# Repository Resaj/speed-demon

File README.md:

# Speed Demon
Speed Demon es mi primer velocista de competición. Ha participado en Alcabot y Cosmobot.

Es un robot bastante casero porque lo hice en 10 días con una plancha de acero que posteriormente cubrí de laca para que no se oxidara.
Para su primera competición tuve que cambiarle la placa del microcontrolador la tarde de antes porque la inicial daba muchos problemas. Le programé el algoritmo PID en una noche y a la mañana siguiente compitió incluso con aceleración en recta programada un rato antes.

Dio muy buenos resultados y quedó en una posición bastante digna, pero pronto fue sustituido por Pumatrón V2 en su versión velocista.
Los programas "actuales" de Speed Demon que he subido al repositorio quedaron en versión beta precisamente por eso.

## Autor
[Rubén Espino San José](https://github.com/Resaj)

## License

Todos estos productos están liberados mediante [Creative Commons Attribution-ShareAlike 4.0 International License](http://creativecommons.org/licenses/by-sa/4.0/).  
_All these products are released under [Creative Commons Attribution-ShareAlike 4.0 International License](http://creativecommons.org/licenses/by-sa/4.0/)._

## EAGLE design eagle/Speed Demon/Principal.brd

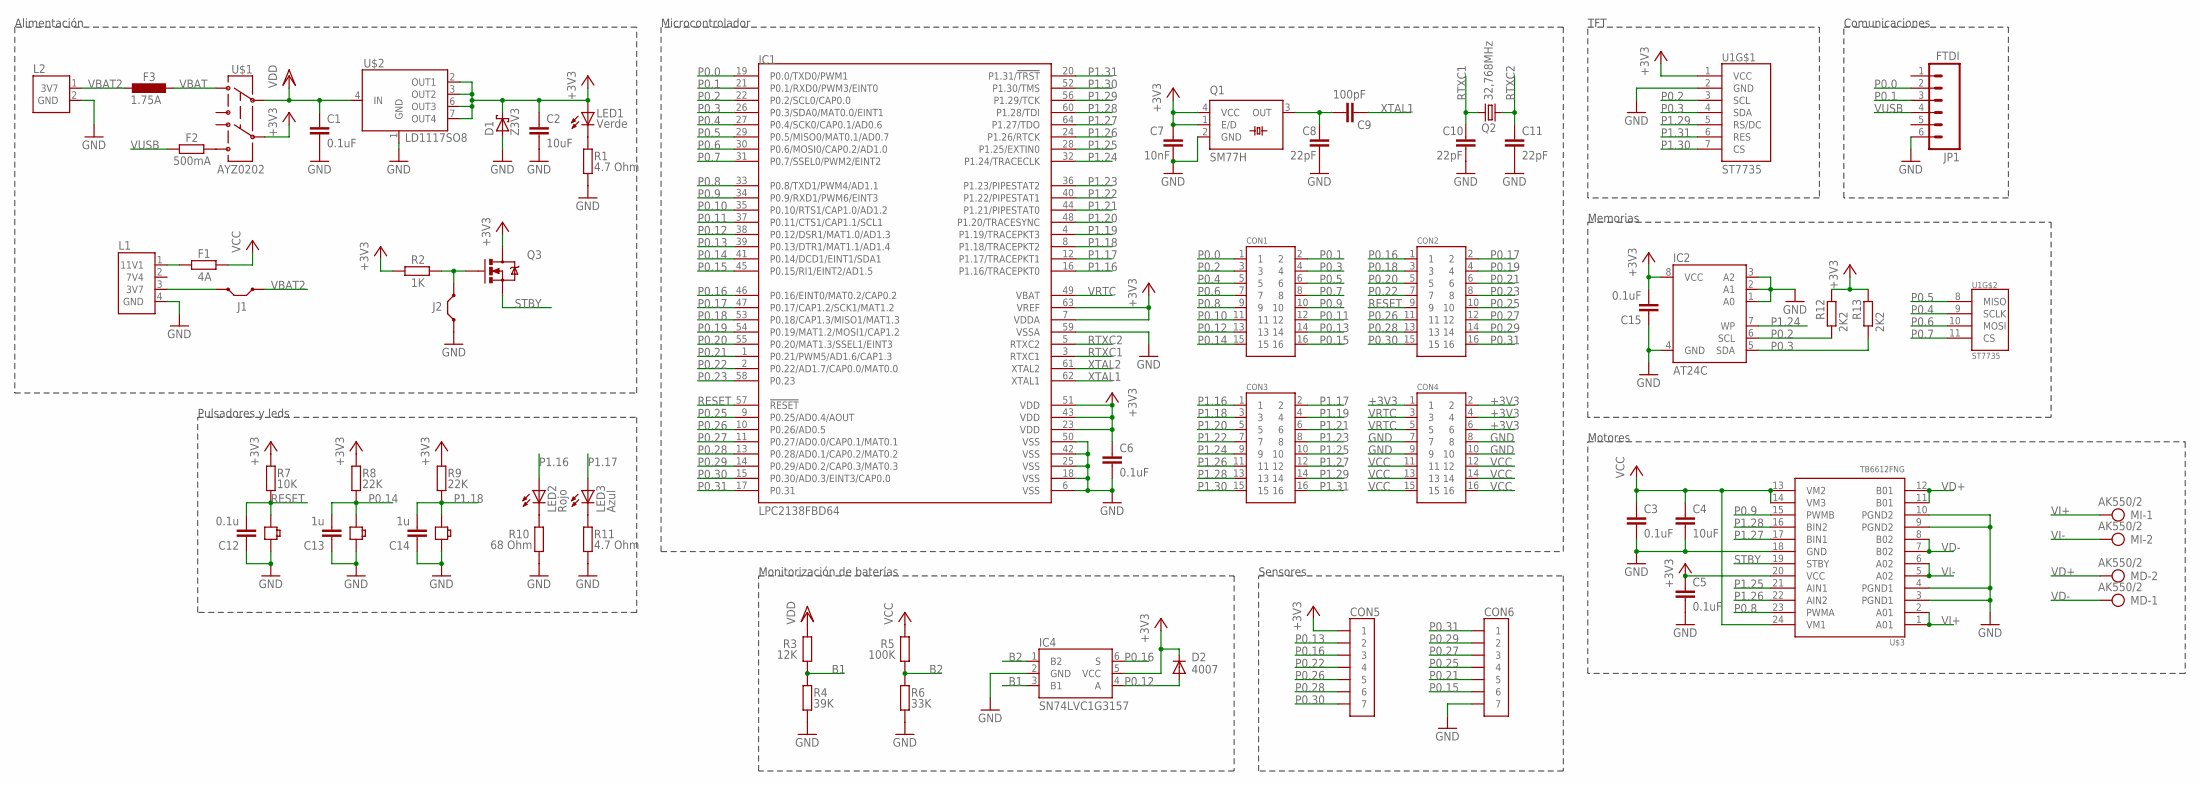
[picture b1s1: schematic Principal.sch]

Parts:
B1: BUTTON-SMD-2P; BUTTON_2P_SMD
C1, C3, C5, C6, C15: 0.1uF; C0805
C2, C4: 10uF; C1206
C7: 10nF; C0805
C8, C10, C11: 22pF; C0805
C9: 100pF; C0805
C12: 0.1u; C0805
C13, C14: 1u; C0805
CON1, CON2, CON3, CON4: 8X2_PIN_2MM_HEMBRA; 8X2_PIN_2MM
CON5, CON6: 7_PINES; 7_PIN_MACHO_SMD_RA
D1: Z3V3; DO35-7
D2: 4007; SOD106-R
F1: 4A; 2920
F2: 500mA; M1206
F3: 1.75A; L1812
IC1: LPC2138FBD64; TSQFP50P1200X1200X160-64N
IC2: AT24C; 8S1
IC4: SN74LVC1G3157; DBV
J1, J2: JUMPERSMD; 2_PIN_VERT_SMD
JP1: FTDI; 1X06_SMD_STRAIGHT
L1: CONECTOR_LIPO_11.1V
L2: CONECTOR_LIPO_3.7V
LED1: Verde; CHIPLED_0805
LED2: Rojo; CHIPLED_0805
LED3: Azul; CHIPLED_0805
LOAD: BUTTON-SMD-2P; BUTTON_2P_SMD
MD: AK550/2
MI: AK550/2
Q1: SM77H
Q2: 32,768MHz; TC38H
Q3: MOSFET-NCHANNELSMD; SOT23-3
R1, R11: 4.7 Ohm; R0805
R2: 1K; R0805
R3: 12K; R0805
R4: 39K; R0805
R5: 100K; R0805
R6: 33K; R0805
R7: 10K; R0805
R8, R9: 22K; R0805
R10: 68 Ohm; R0805
R12, R13: 2K2; R0805
RESET: BUTTON-SMD-2P; BUTTON_2P_SMD
U1: ST7735
U$1: AYZ0202
U$2: LD1117SO8; SO8
U$3: TB6612FNG; SSOP24

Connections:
7V4: L1.2 (7V4)
+3V3: C2.1, C5.1, C6.1, C7.1, C15.2, CON4.1, CON4.2, CON4.4, CON4.6, CON5.P$1 (1), D1.C, D2.C, IC1.7 (VDDA), IC1.23 (VDD), IC1.43 (VDD), IC1.51 (VDD), IC1.63 (VREF), IC2.8 (VCC), IC4.5 (VCC), LED1.A, Q1.1 (E/D), Q1.4 (VCC), Q3.3 (D), R2.2, R7.2, R8.2, R9.2, R12.2, R13.2, U1.1 (VCC), U$1.5, U$2.2 (OUT1), U$2.3 (OUT2), U$2.6 (OUT3), U$2.7 (OUT4), U$3.20 (VCC)
B1: IC4.3 (B1), R3.1, R4.2
B2: IC4.1 (B2), R5.1, R6.2
GND: B1.P$2, C1.2, C2.2, C3.2, C4.2, C5.2, C6.2, C7.2, C8.2, C10.2, C11.2, C12.1, C13.1, C14.1, C15.1, CON4.7, CON4.8, CON4.9, CON4.10, CON6.P$7 (7), D1.A, IC1.6 (VSS), IC1.18 (VSS), IC1.25 (VSS), IC1.42 (VSS), IC1.50 (VSS), IC1.59 (VSSA), IC2.1 (A0), IC2.2 (A1), IC2.3 (A2), IC2.4 (GND), IC4.2 (GND), J2.1, JP1.6, L1.4 (GND), L2.2 (GND), LOAD.P$2, Q1.2 (GND), R1.2, R4.1, R6.1, R10.2, R11.2, RESET.P$2, U1.2 (GND), U$2.1 (GND), U$3.3 (PGND1), U$3.4 (PGND1), U$3.9 (PGND2), U$3.10 (PGND2), U$3.18 (GND)
unnamed: LED2.C, R10.1
unnamed: LED3.C, R11.1
unnamed: J2.2, Q3.1 (G), R2.1
unnamed: F2.1, U$1.4 (6)
unnamed: F1.1, L1.1 (11V1)
unnamed: J1.2, L1.3 (3V7)
unnamed: LED1.C, R1.1
unnamed: C8.1, C9.1, Q1.3 (OUT)
P0.0: CON1.1, IC1.19 (P0.0/TXD0/PWM1), JP1.2
P0.1: CON1.2, IC1.21 (P0.1/RXD0/PWM3/EINT0), JP1.3
P0.2: CON1.3, IC1.22 (P0.2/SCL0/CAP0.0), IC2.6 (SCL), R12.1, U1.3 (SCL)
P0.3: CON1.4, IC1.26 (P0.3/SDA0/MAT0.0/EINT1), IC2.5 (SDA), R13.1, U1.4 (SDA)
P0.4: CON1.5, IC1.27 (P0.4/SCK0/CAP0.1/AD0.6), U1.9 (SCLK)
P0.5: CON1.6, IC1.29 (P0.5/MISO0/MAT0.1/AD0.7), U1.8 (MISO)
P0.6: CON1.7, IC1.30 (P0.6/MOSI0/CAP0.2/AD1.0), U1.10 (MOSI)
P0.7: CON1.8, IC1.31 (P0.7/SSEL0/PWM2/EINT2), U1.11 (CS)
P0.8: CON1.9, IC1.33 (P0.8/TXD1/PWM4/AD1.1), U$3.23 (PWMA)
P0.9: CON1.10, IC1.34 (P0.9/RXD1/PWM6/EINT3), U$3.15 (PWMB)
P0.10: CON1.11, IC1.35 (P0.10/RTS1/CAP1.0/AD1.2)
P0.11: CON1.12, IC1.37 (P0.11/CTS1/CAP1.1/SCL1)
P0.12: CON1.13, D2.A, IC1.38 (P0.12/DSR1/MAT1.0/AD1.3), IC4.4 (A)
P0.13: CON1.14, CON5.P$2 (2), IC1.39 (P0.13/DTR1/MAT1.1/AD1.4)
P0.14: C13.2, CON1.15, IC1.41 (P0.14/DCD1/EINT1/SDA1), LOAD.1, R8.1
P0.15: CON1.16, CON6.P$6 (6), IC1.45 (P0.15/RI1/EINT2/AD1.5)
P0.16: CON2.1, CON5.P$3 (3), IC1.46 (P0.16/EINT0/MAT0.2/CAP0.2), IC4.6 (S)
P0.17: CON2.2, IC1.47 (P0.17/CAP1.2/SCK1/MAT1.2)
P0.18: CON2.3, IC1.53 (P0.18/CAP1.3/MISO1/MAT1.3)
P0.19: CON2.4, IC1.54 (P0.19/MAT1.2/MOSI1/CAP1.2)
P0.20: CON2.5, IC1.55 (P0.20/MAT1.3/SSEL1/EINT3)
P0.21: CON2.6, CON6.P$5 (5), IC1.1 (P0.21/PWM5/AD1.6/CAP1.3)
P0.22: CON2.7, CON5.P$4 (4), IC1.2 (P0.22/AD1.7/CAP0.0/MAT0.0)
P0.23: CON2.8, IC1.58 (P0.23)
P0.25: CON2.10, CON6.P$4 (4), IC1.9 (P0.25/AD0.4/AOUT)
P0.26: CON2.11, CON5.P$5 (5), IC1.10 (P0.26/AD0.5)
P0.27: CON2.12, CON6.P$3 (3), IC1.11 (P0.27/AD0.0/CAP0.1/MAT0.1)
P0.28: CON2.13, CON5.P$6 (6), IC1.13 (P0.28/AD0.1/CAP0.2/MAT0.2)
P0.29: CON2.14, CON6.P$2 (2), IC1.14 (P0.29/AD0.2/CAP0.3/MAT0.3)
P0.30: CON2.15, CON5.P$7 (7), IC1.15 (P0.30/AD0.3/EINT3/CAP0.0)
P0.31: CON2.16, CON6.P$1 (1), IC1.17 (P0.31)
P1.16: CON3.1, IC1.16 (P1.16/TRACEPKT0), LED2.A
P1.17: CON3.2, IC1.12 (P1.17/TRACEPKT1), LED3.A
P1.18: B1.1, C14.2, CON3.3, IC1.8 (P1.18/TRACEPKT2), R9.1
P1.19: CON3.4, IC1.4 (P1.19/TRACEPKT3)
P1.20: CON3.5, IC1.48 (P1.20/TRACESYNC)
P1.21: CON3.6, IC1.44 (P1.21/PIPESTAT0)
P1.22: CON3.7, IC1.40 (P1.22/PIPESTAT1)
P1.23: CON3.8, IC1.36 (P1.23/PIPESTAT2)
P1.24: CON3.9, IC1.32 (P1.24/TRACECLK), IC2.7 (WP)
P1.25: CON3.10, IC1.28 (P1.25/EXTIN0), U$3.21 (AIN1)
P1.26: CON3.11, IC1.24 (P1.26/RTCK), U$3.22 (AIN2)
P1.27: CON3.12, IC1.64 (P1.27/TDO), U$3.17 (BIN1)
P1.28: CON3.13, IC1.60 (P1.28/TDI), U$3.16 (BIN2)
P1.29: CON3.14, IC1.56 (P1.29/TCK), U1.5 (RS/DC)
P1.30: CON3.15, IC1.52 (P1.30/TMS), U1.7 (CS)
P1.31: CON3.16, IC1.20 (P1.31/!TRST), U1.6 (RES)
RESET: C12.2, CON2.9, IC1.57 (!RESET), R7.1, RESET.1
RTXC1: C10.1, IC1.3 (RTXC1), Q2.2
RTXC2: C11.1, IC1.5 (RTXC2), Q2.1
STBY: Q3.2 (S), U$3.19 (STBY)
VBAT: F3.1, U$1.3 (1)
VBAT2: F3.2, J1.1, L2.1 (3V7)
VCC: C3.1, C4.1, CON4.11, CON4.12, CON4.13, CON4.14, CON4.15, CON4.16, F1.2, R5.2, U$3.13 (VM2), U$3.14 (VM3), U$3.24 (VM1)
VD+: MD.2, U$3.11 (B01), U$3.12 (B01)
VD-: MD.1, U$3.7 (B02), U$3.8 (B02)
VDD: C1.1, R3.2, U$1.2, U$2.4 (IN)
VI+: MI.1, U$3.1 (A01), U$3.2 (A01)
VI-: MI.2, U$3.5 (A02), U$3.6 (A02)
VRTC: CON4.3, CON4.5, IC1.49 (VBAT)
VUSB: F2.2, JP1.4
XTAL1: C9.2, IC1.62 (XTAL1)
XTAL2: IC1.61 (XTAL2)

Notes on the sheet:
Memorias
Alimentación
Sensores
Comunicaciones
Motores
Pulsadores y leds
Microcontrolador
Monitorización de baterías
TFT

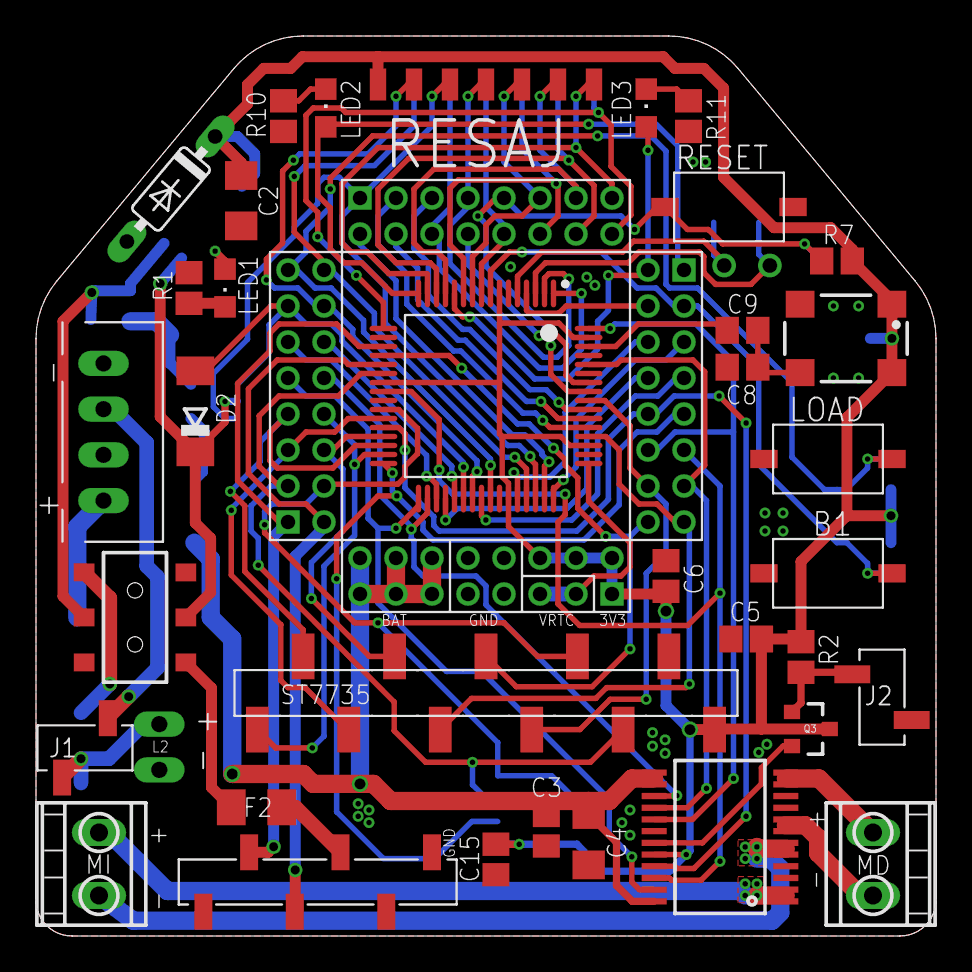
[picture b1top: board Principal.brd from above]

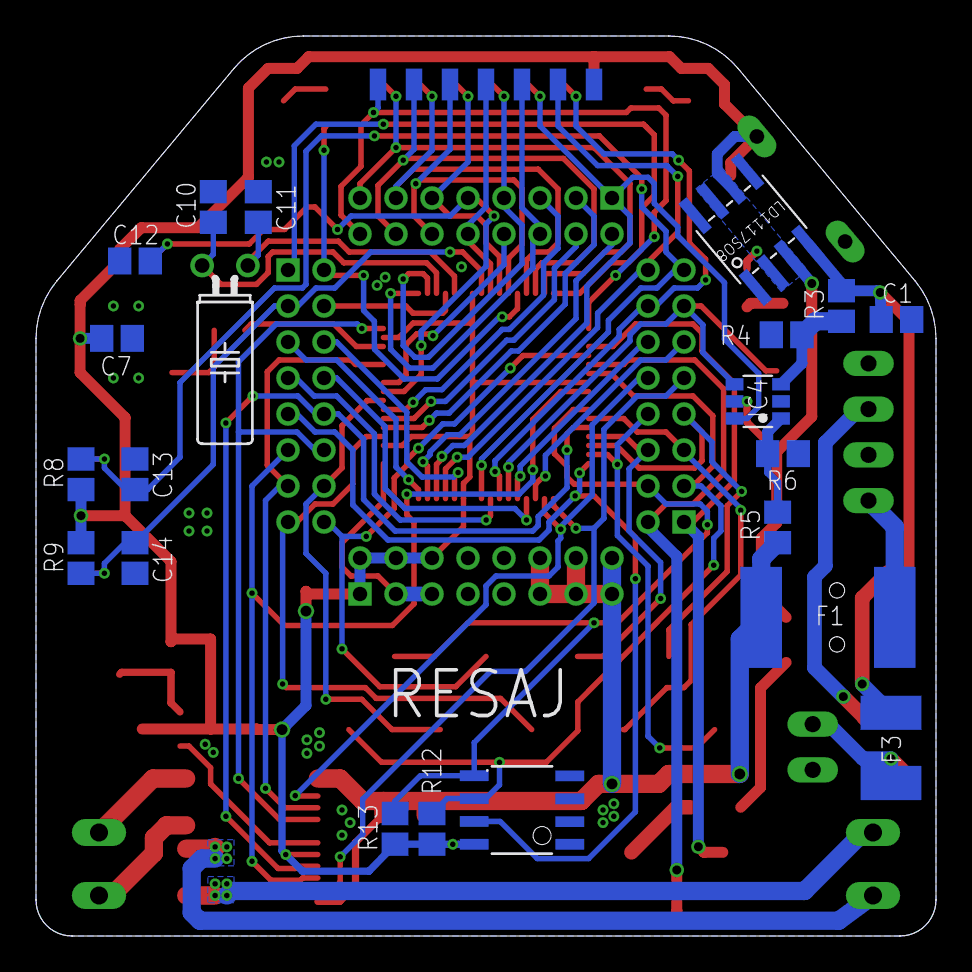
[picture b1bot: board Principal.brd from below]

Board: 2 copper layers, 50.0 x 50.0 mm, 62 parts (22 on the bottom side), 74 nets.

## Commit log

2017-03-02 Archivos PINSEL anteriores modificados
